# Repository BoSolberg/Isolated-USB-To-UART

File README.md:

# Isolated-USB-To-UART
### A Simple 5kV Isolated USB To UART Bridge

The isolated USB to UART Bridge works with Baudrates from 300 baud to 3 Mbaud.</br>
It can withstand 5000Vrms for 1 minute.</br>
And 565Vpeak Continuously, without destroying your computer.</br>

It can opperate with a circuit voltage from 1.8V to 5V.

<p xmlns:dct="http://purl.org/dc/terms/" xmlns:cc="http://creativecommons.org/ns#" class="license-text">This work   is licensed under <a rel="license" href="https://creativecommons.org/licenses/by-sa/4.0">CC BY-SA 4.0</a></p>

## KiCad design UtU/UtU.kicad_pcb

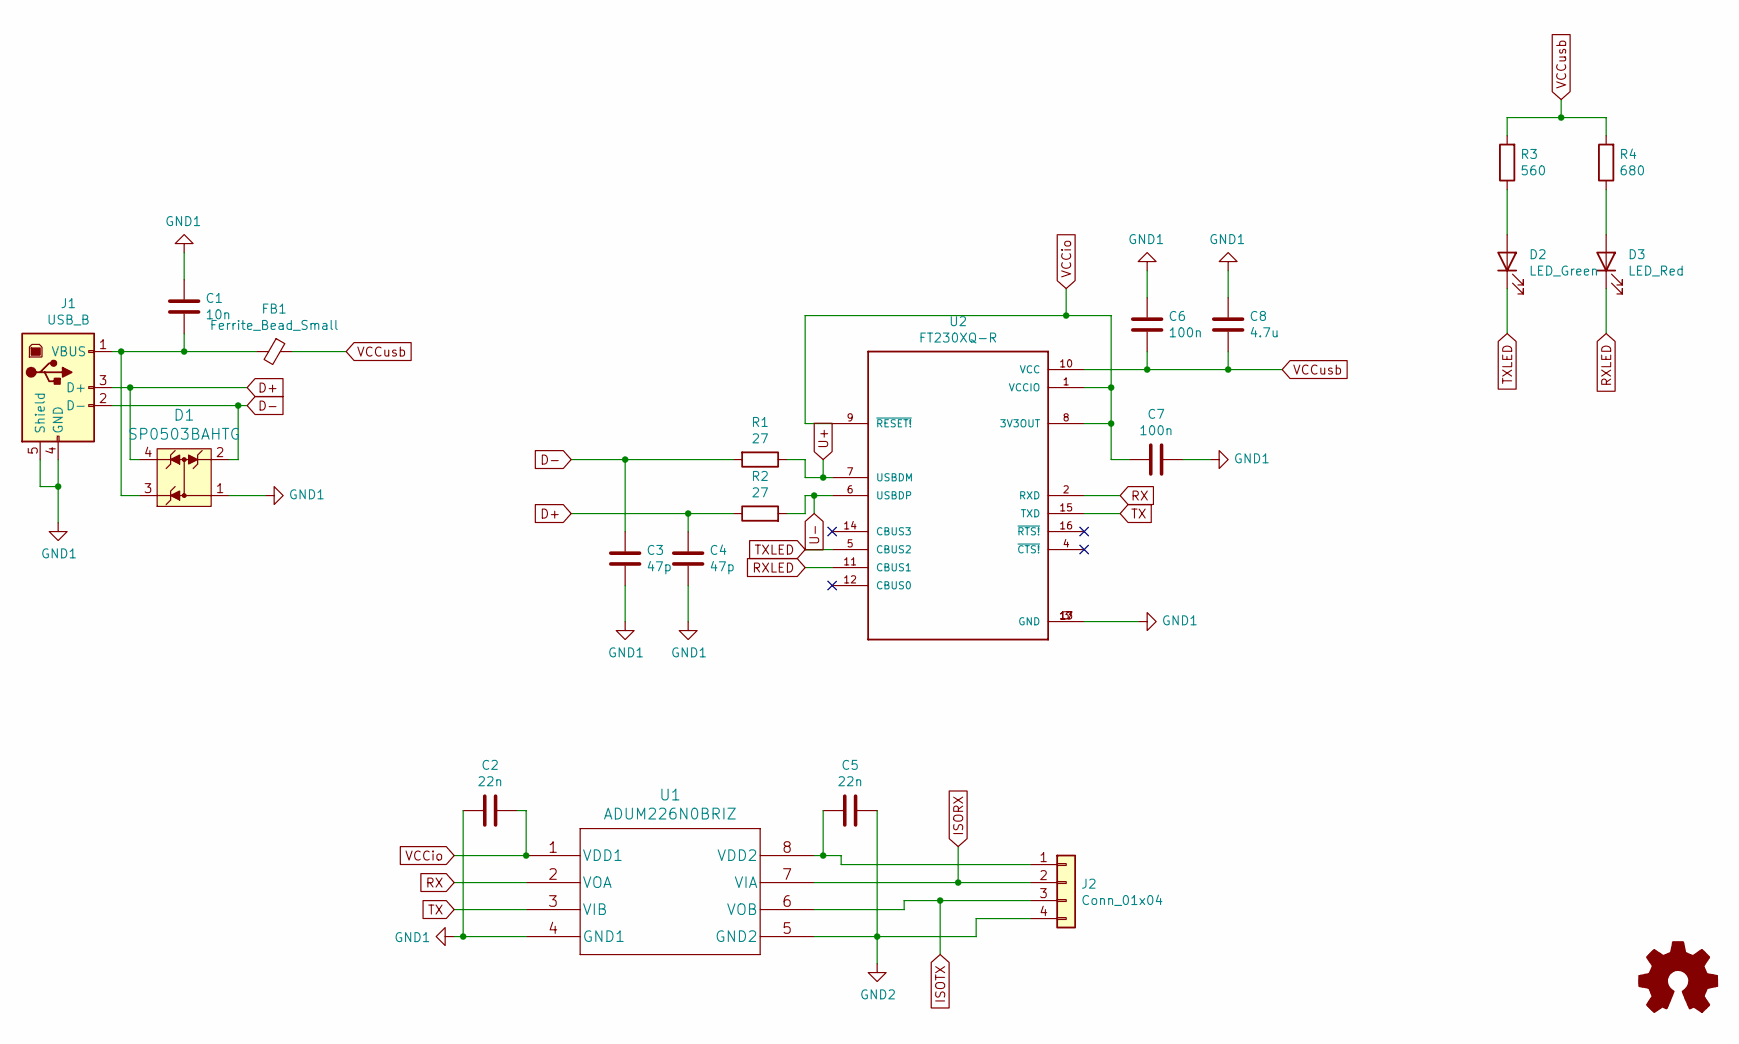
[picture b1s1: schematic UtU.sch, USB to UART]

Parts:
C1: 10n; C_0805_2012Metric; MPN AC0805KRX7R7BB103; Digi-Key_PN 311-3161-1-ND
C2, C5: 22n; C_0805_2012Metric; MPN AC0805KRX7R7BB223; Digi-Key_PN 311-3163-1-ND
C3, C4: 47p; C_0805_2012Metric; MPN CC0805JRNPO9BN470; Digi-Key_PN 311-1107-1-ND
C6, C7: 100n; C_0805_2012Metric; MPN CC0805KRX7R7BB104; Digi-Key_PN 311-1142-1-ND
C8: 4.7u; C_0805_2012Metric; MPN CC0805KKX5R7BB475; Digi-Key_PN 311-1867-1-ND
D1: SP0503BAHTG; SOT-143-4; MPN SP0503BAHTG; Digi-Key_PN F2715CT-ND
D2: LED_Green; D_0805_2012Metric; MPN LG R971-KN-1; Digi-Key_PN 475-1410-1-ND
D3: LED_Red; D_0805_2012Metric; MPN LH R974-LP-1; Digi-Key_PN 475-1415-1-ND
FB1: Ferrite_Bead_Small; R_0805_2012Metric; MPN MI0805K601R-10; Digi-Key_PN 240-2390-1-ND
J1: USB_B; CUI_UJ2-BH-1-TH; MPN UJ2-BH-1-TH; Digi-Key_PN 102-3999-ND
J2: Conn_01x04; PinHeader_1x04_P2.54mm_Horizontal; MPN PH1RB-04-UA; Digi-Key_PN 2057-PH1RB-04-UA-ND
R1, R2: 27; R_0805_2012Metric; MPN RC0805FR-0727RL; Digi-Key_PN 311-27.0CRCT-ND
R3: 560; R_0805_2012Metric; MPN RC0805JR-07560RL; Digi-Key_PN 311-560ARCT-ND
R4: 680; R_0805_2012Metric; MPN RC0805JR-07680RL; Digi-Key_PN 311-680ARCT-ND
U1: ADUM226N0BRIZ; MPN ADUM226N0BRIZ; Digi-Key_PN ADUM226N0BRIZ-ND
U2: FT230XQ-R; QFN65P400X400X80-17N; MPN FT230XQ-R; Digi-Key_PN 768-1130-1-ND

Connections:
D+: C4.1, D1.4, J1.3 (D+), R2.1
D-: C3.1, D1.2, J1.2 (D-), R1.2
GND1: C1.1, C2.2, C3.2, C4.2, C6.1, C7.2, C8.1, D1.1, J1.4 (GND), J1.5 (Shield), U1.4 (GND1), U2.3 (GND), U2.13 (GND), U2.17 (GND)
GND2: C5.1, J2.4, U1.5 (GND2)
ISORX: J2.2, U1.7 (VIA)
ISOTX: J2.3, U1.6 (VOB)
unnamed: C1.2, D1.3, FB1.2, J1.1 (VBUS)
unnamed: C5.2, J2.1, U1.8 (VDD2)
unnamed: D2.2 (A), R3.1
unnamed: D3.2 (A), R4.1
RX: U1.2 (VOA), U2.2 (RXD)
RXLED: D3.1 (K), U2.11 (CBUS1)
TX: U1.3 (VIB), U2.15 (TXD)
TXLED: D2.1 (K), U2.5 (CBUS2)
U+: R1.1, U2.7 (USBDM)
U-: R2.2, U2.6 (USBDP)
VCCio: C2.1, C7.1, U1.1 (VDD1), U2.1 (VCCIO), U2.8 (3V3OUT), U2.9 (~RESET!~)
VCCusb: C6.2, C8.2, FB1.1, R3.2, R4.2, U2.10 (VCC)

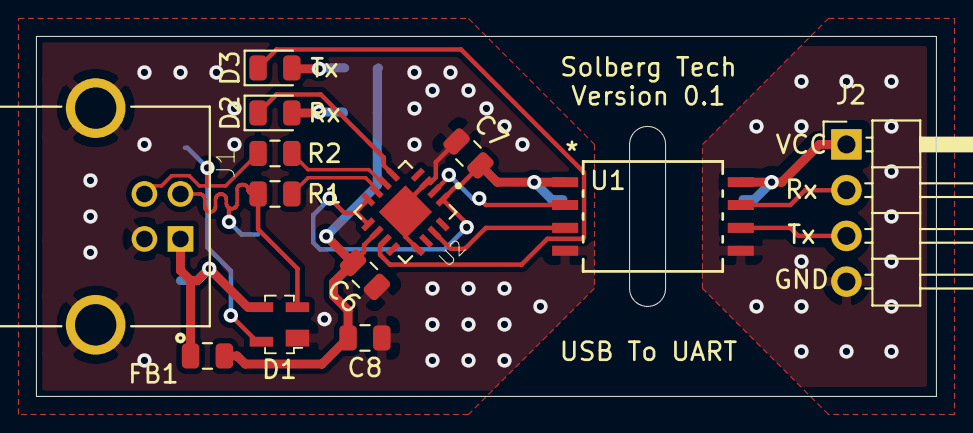
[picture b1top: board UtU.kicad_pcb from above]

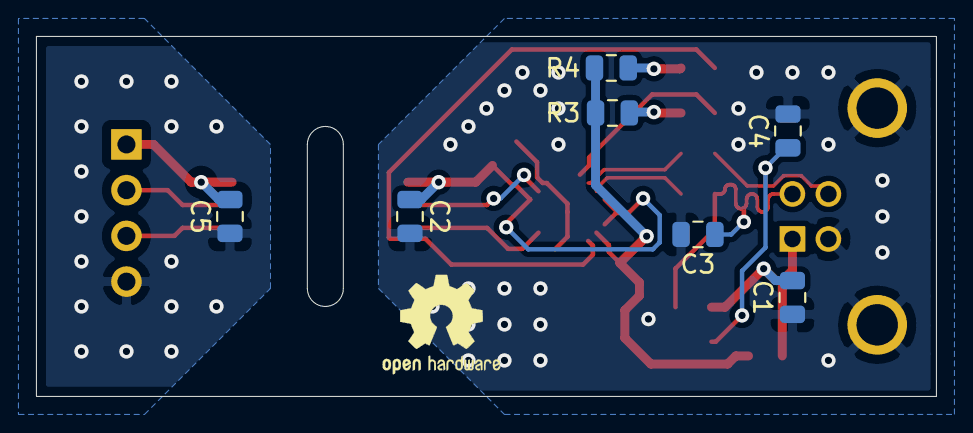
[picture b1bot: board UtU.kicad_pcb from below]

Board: 2 copper layers, 50.0 x 20.0 mm, 20 parts (7 on the bottom side), 18 nets.

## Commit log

2020-09-02 Create LICENSE
2020-09-02 Rename UtU/UtU.csv to BOM/UtU.csv

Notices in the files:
parts and their libraries:
Copyright 2016 Accelerated Designs. All rights reserved.
